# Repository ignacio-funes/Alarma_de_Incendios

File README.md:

# Alarma de Incendios
## Introducción
Mi proyecto consistirá en armar un sistema de alarma de incendios, que sea suficientemente confiable para ser utilizado en un ambiente de trabajo. Esto requerirá una serie de funciones que aprovecharán las posibilidades del ESP-32.

## Objetivos
1. Responder a fuegos sin demoras significativas.
   
2. Alertar, de formas visibles, a las personas en riesgo.
   
3. Permitir acceso rápido al estado del sistema a través de la red.
   
## Alcances
- Mantener y actualizar una página web. Para acceder, hay que conectarse a la red del módulo ESP32.

- Monitorear el estado de una sola habitación.

- Alimentado con una batería de 9V, tendrá una autonomía limitada.

## Funcionalidad
El sistema tomará en cuenta las lecturas tanto de un sensor infrarrojo como de un detector de humo para su lógica. En caso de activarse cualquiera de los sensores, el sistema activará su estado de alarma. Se encenderán el buzzer y el led rojo, y se enviarán alertas a la red. De lo contrario, se encenderá el led verde, y se enviarán actualizaciones a la red en intervalos regulares.

## Propuestas a futuro
El sistema podría ser adaptado para controlar múltiples sistemas, distintas oficinas en un edificio, por ejemplo. Sería posible, entonces, monitorear el estado de cada una, y en caso de incendio, controlar el avance del fuego. Esto se podría combinar con otras aplicaciones, como sistemas de vigilancia o control de ambiente, tanto para la mejor prevención de accidentes como para un espacio de trabajo más cómodo y saludable. 

## Más información
En las carpetas del repositorio se encuentra más información del proyecto, y los archivos necesarios para hacerlo funcionar.

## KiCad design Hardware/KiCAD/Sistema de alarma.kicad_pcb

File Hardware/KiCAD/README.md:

# KiCAD
En esta carpeta se cargarán los cambios en el diseño de el sistema, tanto en su esquemático como en su PCB.

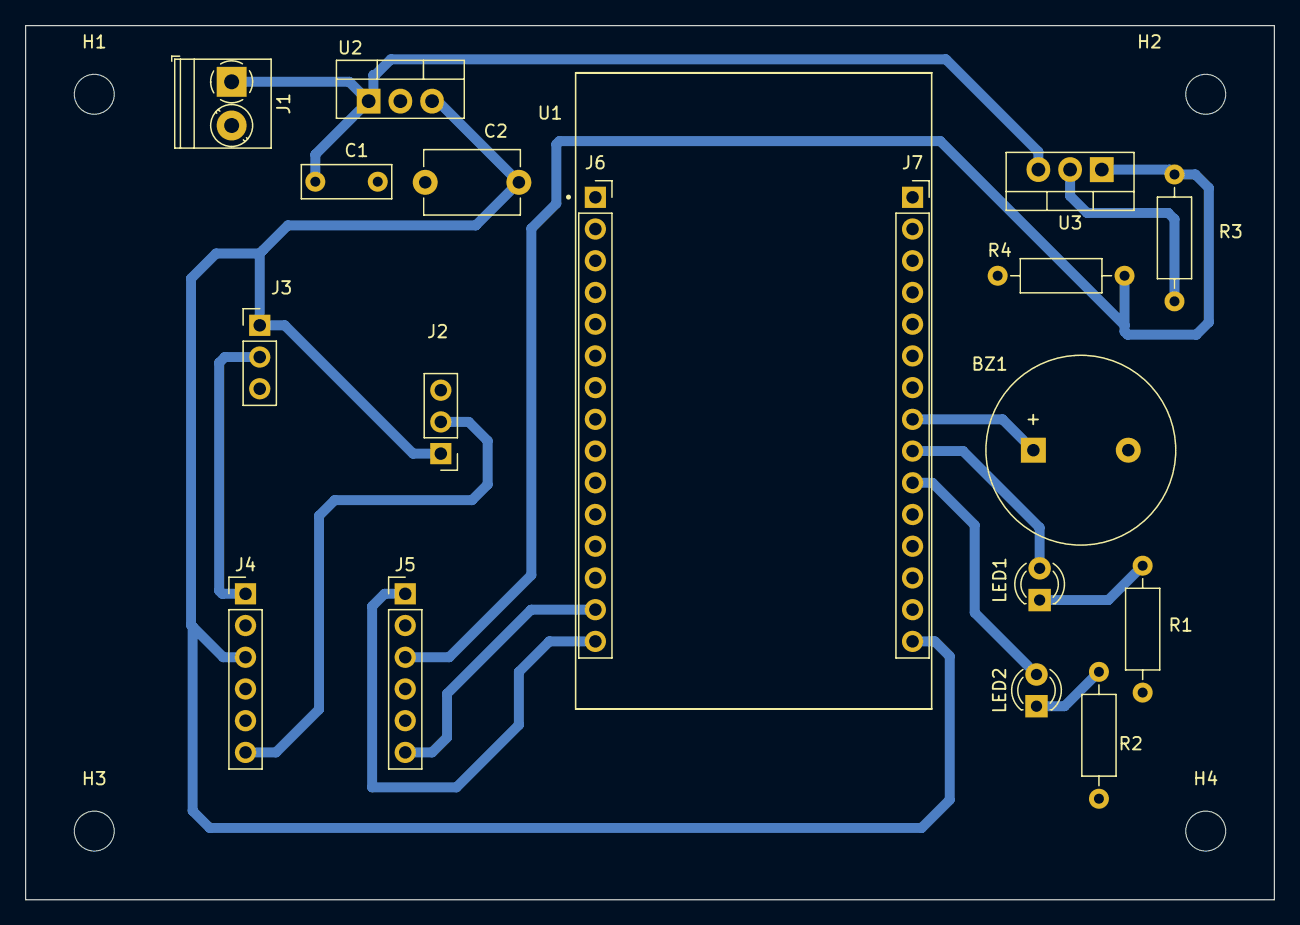
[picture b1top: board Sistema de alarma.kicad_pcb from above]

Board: 2 copper layers, 100.0 x 70.0 mm, 23 parts (0 on the bottom side), 14 nets.

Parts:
BZ1: Buzzer; Buzzer_15x7.5RM7.6
C1: 0,22uF; C_Disc_D7.0mm_W2.5mm_P5.00mm
C2: 0,1uF, ceramic disc; C_Disc_D7.5mm_W5.0mm_P7.50mm
H1, H2, H3, H4: MountingHole; MountingHole_3.2mm_M3
J1: Alimentación; TerminalBlock_Phoenix_PT-1,5-2-3.5-H_1x02_P3.50mm_Horizontal
J2: MQ2 Conn; PinHeader_1x03_P2.54mm_Vertical
J3: IR R Pins; PinHeader_1x03_P2.54mm_Vertical
J4, J5: Conn_01x06_Socket; PinHeader_1x06_P2.54mm_Vertical
J6, J7: Conn_01x15_Socket; PinSocket_1x15_P2.54mm_Vertical
LED1: Rojo; LED_D3.0mm
LED2: Verde; LED_D3.0mm
R1: 115; R_Axial_DIN0207_L6.3mm_D2.5mm_P10.16mm_Horizontal
R2: 100; R_Axial_DIN0207_L6.3mm_D2.5mm_P10.16mm_Horizontal
R3: 1k; R_Axial_DIN0207_L6.3mm_D2.5mm_P10.16mm_Horizontal
R4: 1,64k; R_Axial_DIN0207_L6.3mm_D2.5mm_P10.16mm_Horizontal
U1: ESP32-DEVKIT-V1; MODULE_ESP32_DEVKIT_V1
U2: LM7805_TO220; TO-220-3_Vertical
U3: LM317_TO-220; TO-220-3_Vertical

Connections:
3,3V: J5.3, R3.2, R4.1, U3.1 (ADJ)
5V: C2.1, J2.1, J3.1, J4.3, J7.15, U2.3 (VO)
+9V: C1.1, J1.1, U2.1 (VI), U3.3 (VI)
/LED1 K: LED1.1 (K), R1.1
/LED2 K: LED2.1 (K), R2.1
/LM317 Vo: R3.1, U3.2 (VO)
Buzzer: BZ1.1 (-), J7.8
Earth: BZ1.2 (+), C1.2, C2.2, J1.2, J2.3, J3.3, J4.4, J5.4, J6.2, J7.14, R1.2, R2.2, R4.2, U2.2 (GND)
IR In: J5.1, J6.15
IR Signal: J3.2, J4.1
LED1: J7.9, LED1.2 (A)
LED2: J7.10, LED2.2 (A)
MQ2 In: J5.6, J6.14
MQ2 Signal: J2.2, J4.6

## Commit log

2024-10-16 Create Componentes
2024-10-16 Create a
2024-10-19 Update Componentes
2024-10-19 Create Versionado
2024-11-17 Rename Componentes to Componentes.md
2024-11-17 Rename LM340.PDF to LM78xx.PDF
2024-11-17 Rename MQ2.pdf to MQ2.md
2024-11-17 Update Versionado
2024-11-20 Rename Hardware/KiCAD/Impresión PCB.pdf to Hardware/Impresión PCB.pdf
